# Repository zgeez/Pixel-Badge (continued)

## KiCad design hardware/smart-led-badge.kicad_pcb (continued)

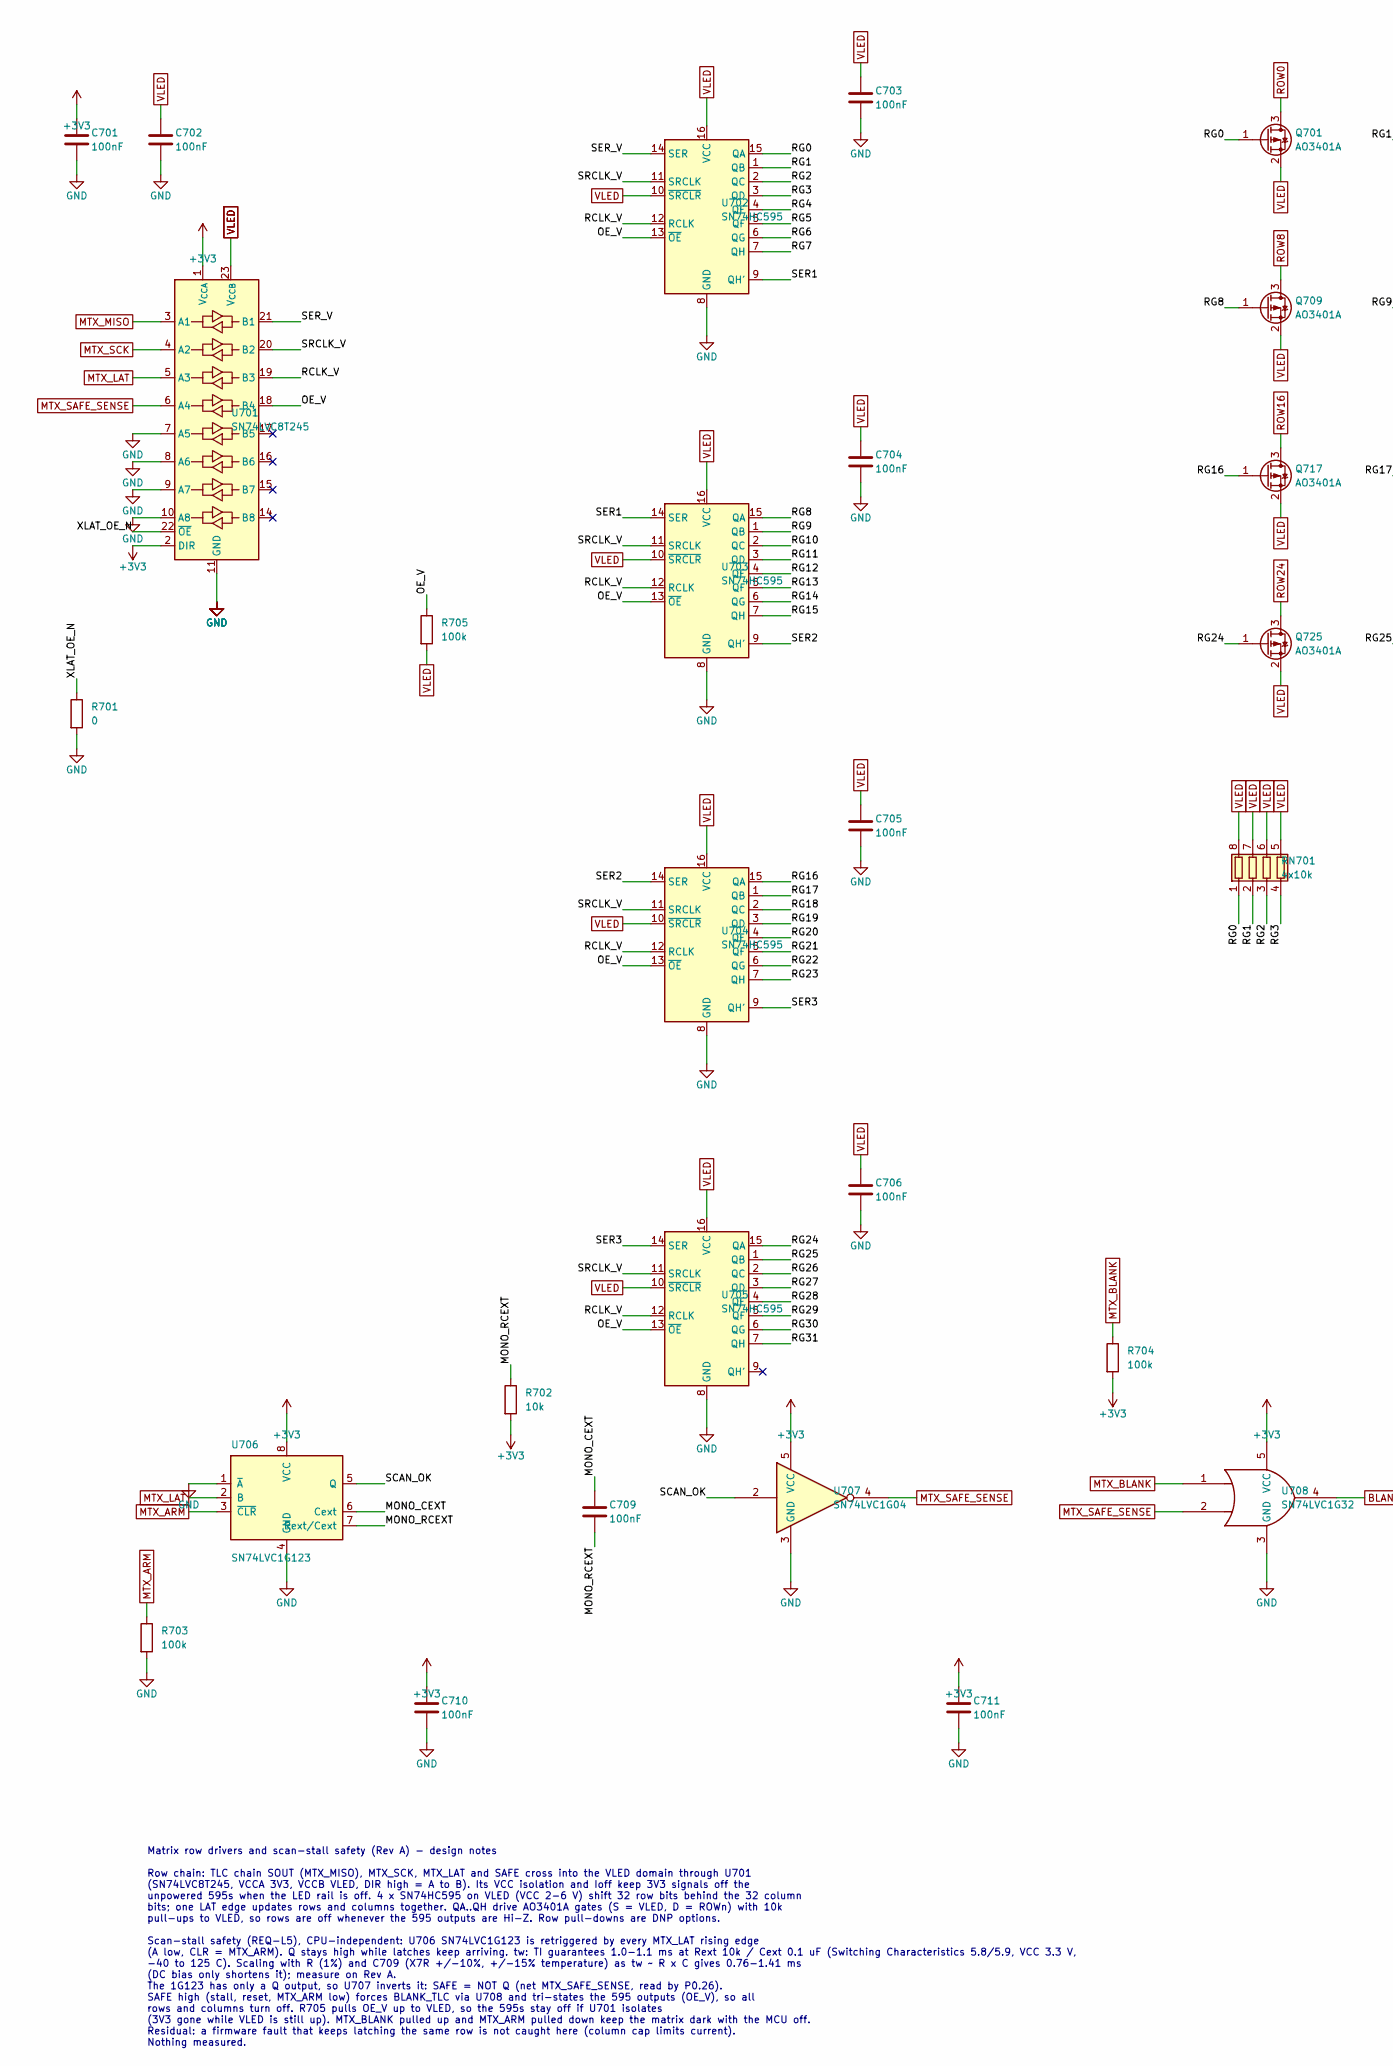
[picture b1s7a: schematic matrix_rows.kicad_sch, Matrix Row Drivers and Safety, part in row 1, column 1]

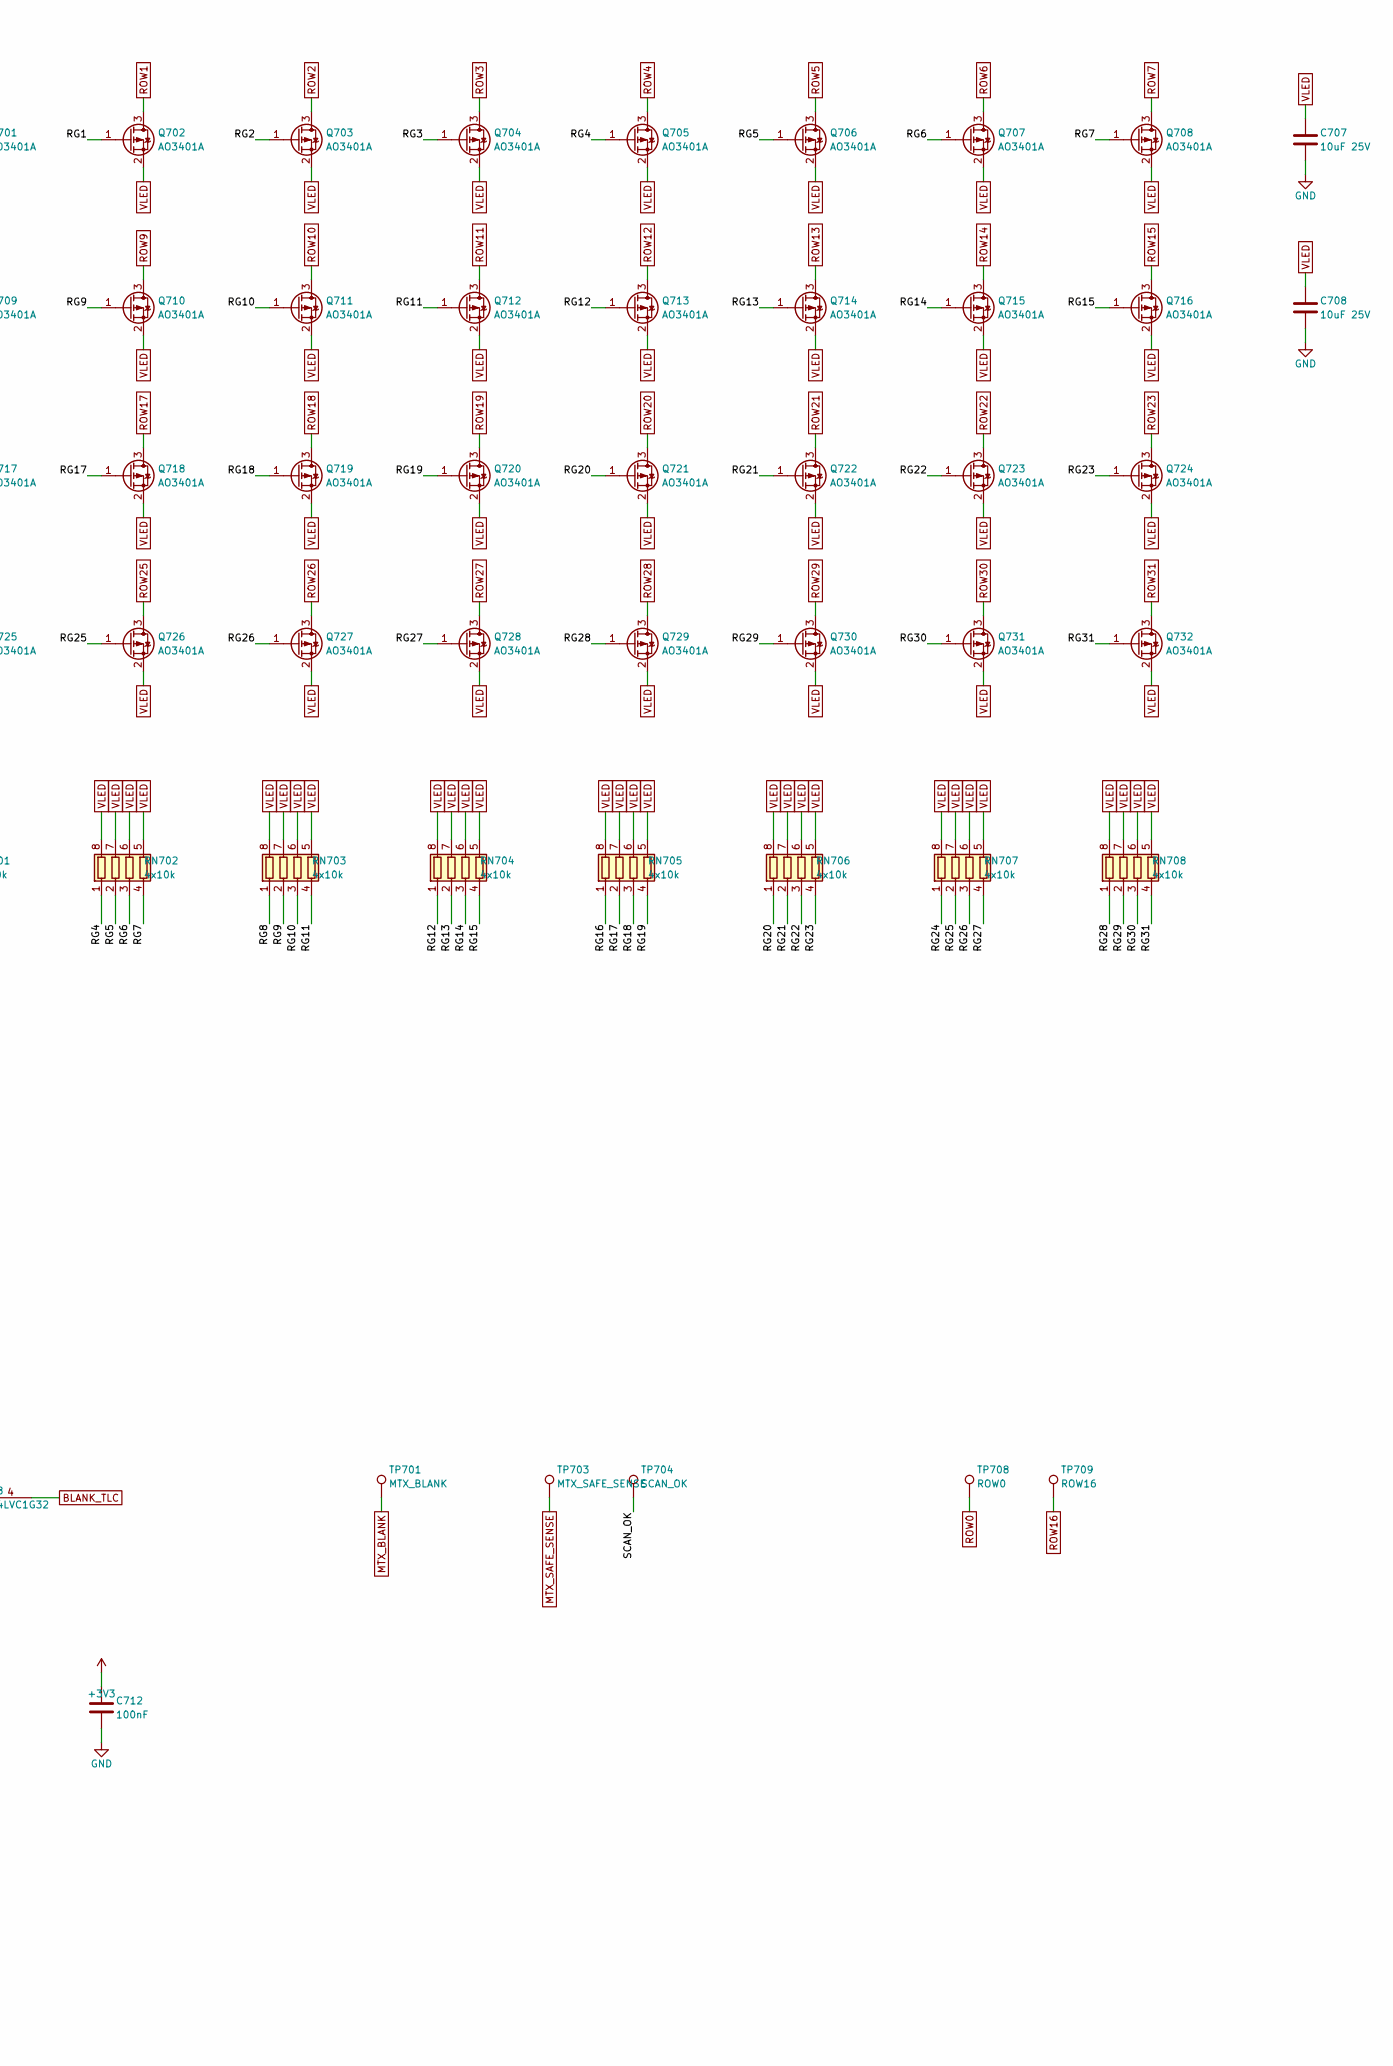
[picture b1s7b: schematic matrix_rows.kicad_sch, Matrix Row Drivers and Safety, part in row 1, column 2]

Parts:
C701, C702, C703, C704, C705, C706, C709, C710, C711, C712: 100nF; C_0402_1005Metric; MPN CL05B104KO5NNNC; LCSC C1525
C707, C708: 10uF 25V; C_0805_2012Metric; MPN CL21A106KAYNNNE; LCSC C15850
Q701, Q702, Q703, Q704, Q705, Q706, Q707, Q708, Q709, Q710, Q711, Q712, Q713, Q714, Q715, Q716, Q717, Q718, Q719, Q720, Q721, Q722, Q723, Q724, Q725, Q726, Q727, Q728, Q729, Q730, Q731, Q732: AO3401A; SOT-23; MPN AO3401A; LCSC C15127
R701: 0; R_0402_1005Metric; MPN 0402WGF0000TCE; LCSC C17168
R702: 10k; R_0402_1005Metric; MPN 0402WGF1002TCE; LCSC C25744
R703, R704, R705: 100k; R_0402_1005Metric; MPN 0402WGF1003TCE; LCSC C25741
RN701, RN702, RN703, RN704, RN705, RN706, RN707, RN708: 4x10k; R_Array_Convex_4x0603; MPN 4D03WGJ0103T5E; LCSC C29718
TP701: MTX_BLANK; TestPoint_Pad_D1.0mm
TP703: MTX_SAFE_SENSE; TestPoint_Pad_D1.0mm
TP704: SCAN_OK; TestPoint_Pad_D1.0mm
TP708: ROW0; TestPoint_Pad_D1.0mm
TP709: ROW16; TestPoint_Pad_D1.0mm
U701: SN74LVC8T245; TSSOP-24_4.4x7.8mm_P0.65mm; MPN SN74LVC8T245PWR; LCSC C27643
U702, U703, U704, U705: SN74HC595; TSSOP-16_4.4x5mm_P0.65mm; MPN SN74HC595PWR; LCSC C273642
U706: SN74LVC1G123; SSOP-8_2.95x2.8mm_P0.65mm; MPN SN74LVC1G123DCTR; LCSC C123302
U707: SN74LVC1G04; SOT-23-5; MPN SN74LVC1G04DBVR; LCSC C7827
U708: SN74LVC1G32; SOT-23-5; MPN SN74LVC1G32DBVR; LCSC C10096

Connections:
+3V3: C701.1, C710.1, C711.1, C712.1, R702.2, R704.2, U701.1 (V_{CCA}), U701.2 (DIR), U706.8 (VCC), U707.5 (VCC), U708.5 (VCC); also elsewhere on the board
/Matrix Row Drivers and Safety/MONO_CEXT: C709.1, U706.6 (Cext)
/Matrix Row Drivers and Safety/MONO_RCEXT: C709.2, R702.1, U706.7 (Rext/Cext)
/Matrix Row Drivers and Safety/OE_V: R705.1, U701.18 (B4), U702.13 (~OE), U703.13 (~OE), U704.13 (~OE), U705.13 (~OE)
/Matrix Row Drivers and Safety/RCLK_V: U701.19 (B3), U702.12 (RCLK), U703.12 (RCLK), U704.12 (RCLK), U705.12 (RCLK)
/Matrix Row Drivers and Safety/RG0: Q701.1 (G), RN701.1 (R1.1), U702.15 (QA)
/Matrix Row Drivers and Safety/RG1: Q702.1 (G), RN701.2 (R2.1), U702.1 (QB)
/Matrix Row Drivers and Safety/RG2: Q703.1 (G), RN701.3 (R3.1), U702.2 (QC)
/Matrix Row Drivers and Safety/RG3: Q704.1 (G), RN701.4 (R4.1), U702.3 (QD)
/Matrix Row Drivers and Safety/RG4: Q705.1 (G), RN702.1 (R1.1), U702.4 (QE)
/Matrix Row Drivers and Safety/RG5: Q706.1 (G), RN702.2 (R2.1), U702.5 (QF)
/Matrix Row Drivers and Safety/RG6: Q707.1 (G), RN702.3 (R3.1), U702.6 (QG)
/Matrix Row Drivers and Safety/RG7: Q708.1 (G), RN702.4 (R4.1), U702.7 (QH)
/Matrix Row Drivers and Safety/RG8: Q709.1 (G), RN703.1 (R1.1), U703.15 (QA)
/Matrix Row Drivers and Safety/RG9: Q710.1 (G), RN703.2 (R2.1), U703.1 (QB)
/Matrix Row Drivers and Safety/RG10: Q711.1 (G), RN703.3 (R3.1), U703.2 (QC)
/Matrix Row Drivers and Safety/RG11: Q712.1 (G), RN703.4 (R4.1), U703.3 (QD)
/Matrix Row Drivers and Safety/RG12: Q713.1 (G), RN704.1 (R1.1), U703.4 (QE)
/Matrix Row Drivers and Safety/RG13: Q714.1 (G), RN704.2 (R2.1), U703.5 (QF)
/Matrix Row Drivers and Safety/RG14: Q715.1 (G), RN704.3 (R3.1), U703.6 (QG)
/Matrix Row Drivers and Safety/RG15: Q716.1 (G), RN704.4 (R4.1), U703.7 (QH)
/Matrix Row Drivers and Safety/RG16: Q717.1 (G), RN705.1 (R1.1), U704.15 (QA)
/Matrix Row Drivers and Safety/RG17: Q718.1 (G), RN705.2 (R2.1), U704.1 (QB)
/Matrix Row Drivers and Safety/RG18: Q719.1 (G), RN705.3 (R3.1), U704.2 (QC)
/Matrix Row Drivers and Safety/RG19: Q720.1 (G), RN705.4 (R4.1), U704.3 (QD)
/Matrix Row Drivers and Safety/RG20: Q721.1 (G), RN706.1 (R1.1), U704.4 (QE)
/Matrix Row Drivers and Safety/RG21: Q722.1 (G), RN706.2 (R2.1), U704.5 (QF)
/Matrix Row Drivers and Safety/RG22: Q723.1 (G), RN706.3 (R3.1), U704.6 (QG)
/Matrix Row Drivers and Safety/RG23: Q724.1 (G), RN706.4 (R4.1), U704.7 (QH)
/Matrix Row Drivers and Safety/RG24: Q725.1 (G), RN707.1 (R1.1), U705.15 (QA)
/Matrix Row Drivers and Safety/RG25: Q726.1 (G), RN707.2 (R2.1), U705.1 (QB)
/Matrix Row Drivers and Safety/RG26: Q727.1 (G), RN707.3 (R3.1), U705.2 (QC)
/Matrix Row Drivers and Safety/RG27: Q728.1 (G), RN707.4 (R4.1), U705.3 (QD)
/Matrix Row Drivers and Safety/RG28: Q729.1 (G), RN708.1 (R1.1), U705.4 (QE)
/Matrix Row Drivers and Safety/RG29: Q730.1 (G), RN708.2 (R2.1), U705.5 (QF)
/Matrix Row Drivers and Safety/RG30: Q731.1 (G), RN708.3 (R3.1), U705.6 (QG)
/Matrix Row Drivers and Safety/RG31: Q732.1 (G), RN708.4 (R4.1), U705.7 (QH)
/Matrix Row Drivers and Safety/SCAN_OK: TP704.1, U706.5 (Q), U707.2
/Matrix Row Drivers and Safety/SER1: U702.9 (QH'), U703.14 (SER)
/Matrix Row Drivers and Safety/SER2: U703.9 (QH'), U704.14 (SER)
/Matrix Row Drivers and Safety/SER3: U704.9 (QH'), U705.14 (SER)
/Matrix Row Drivers and Safety/SER_V: U701.21 (B1), U702.14 (SER)
/Matrix Row Drivers and Safety/SRCLK_V: U701.20 (B2), U702.11 (SRCLK), U703.11 (SRCLK), U704.11 (SRCLK), U705.11 (SRCLK)
/Matrix Row Drivers and Safety/XLAT_OE_N: R701.1, U701.22 (~OE)
BLANK_TLC: U708.4; also elsewhere on the board
GND: C701.2, C702.2, C703.2, C704.2, C705.2, C706.2, C707.2, C708.2, C710.2, C711.2, C712.2, R701.2, R703.2, U701.7 (A5), U701.8 (A6), U701.9 (A7), U701.10 (A8), U701.11 (GND), U701.12 (GND), U701.13 (GND), U702.8 (GND), U703.8 (GND), U704.8 (GND), U705.8 (GND), U706.1 (~A), U706.4 (GND), U707.3 (GND), U708.3 (GND); also elsewhere on the board
MTX_ARM: R703.1, U706.3 (~CLR); also elsewhere on the board
MTX_BLANK: R704.1, TP701.1, U708.1; also elsewhere on the board
MTX_LAT: U701.5 (A3), U706.2 (B); also elsewhere on the board
MTX_MISO: U701.3 (A1); also elsewhere on the board
MTX_SAFE_SENSE: TP703.1, U701.6 (A4), U707.4, U708.2; also elsewhere on the board
MTX_SCK: U701.4 (A2); also elsewhere on the board
ROW0: Q701.3 (D), TP708.1; also elsewhere on the board
ROW1: Q702.3 (D); also elsewhere on the board
ROW2: Q703.3 (D); also elsewhere on the board
ROW3: Q704.3 (D); also elsewhere on the board
ROW4: Q705.3 (D); also elsewhere on the board
ROW5: Q706.3 (D); also elsewhere on the board
ROW6: Q707.3 (D); also elsewhere on the board
ROW7: Q708.3 (D); also elsewhere on the board
ROW8: Q709.3 (D); also elsewhere on the board
ROW9: Q710.3 (D); also elsewhere on the board
ROW10: Q711.3 (D); also elsewhere on the board
ROW11: Q712.3 (D); also elsewhere on the board
ROW12: Q713.3 (D); also elsewhere on the board
ROW13: Q714.3 (D); also elsewhere on the board
ROW14: Q715.3 (D); also elsewhere on the board
ROW15: Q716.3 (D); also elsewhere on the board
ROW16: Q717.3 (D), TP709.1; also elsewhere on the board
ROW17: Q718.3 (D); also elsewhere on the board
ROW18: Q719.3 (D); also elsewhere on the board
ROW19: Q720.3 (D); also elsewhere on the board
ROW20: Q721.3 (D); also elsewhere on the board
ROW21: Q722.3 (D); also elsewhere on the board
ROW22: Q723.3 (D); also elsewhere on the board
ROW23: Q724.3 (D); also elsewhere on the board
ROW24: Q725.3 (D); also elsewhere on the board
ROW25: Q726.3 (D); also elsewhere on the board
ROW26: Q727.3 (D); also elsewhere on the board
ROW27: Q728.3 (D); also elsewhere on the board
ROW28: Q729.3 (D); also elsewhere on the board
ROW29: Q730.3 (D); also elsewhere on the board
ROW30: Q731.3 (D); also elsewhere on the board
ROW31: Q732.3 (D); also elsewhere on the board
VLED: C702.1, C703.1, C704.1, C705.1, C706.1, C707.1, C708.1, Q701.2 (S), Q702.2 (S), Q703.2 (S), Q704.2 (S), Q705.2 (S), Q706.2 (S), Q707.2 (S), Q708.2 (S), Q709.2 (S), Q710.2 (S), Q711.2 (S), Q712.2 (S), Q713.2 (S), Q714.2 (S), Q715.2 (S), Q716.2 (S), Q717.2 (S), Q718.2 (S), Q719.2 (S), Q720.2 (S), Q721.2 (S), Q722.2 (S), Q723.2 (S), Q724.2 (S), Q725.2 (S), Q726.2 (S), Q727.2 (S), Q728.2 (S), Q729.2 (S), Q730.2 (S), Q731.2 (S), Q732.2 (S), R705.2, RN701.5 (R4.2), RN701.6 (R3.2), RN701.7 (R2.2), RN701.8 (R1.2), RN702.5 (R4.2), RN702.6 (R3.2), RN702.7 (R2.2), RN702.8 (R1.2), RN703.5 (R4.2), RN703.6 (R3.2), RN703.7 (R2.2), RN703.8 (R1.2), RN704.5 (R4.2), RN704.6 (R3.2), RN704.7 (R2.2), RN704.8 (R1.2), RN705.5 (R4.2), RN705.6 (R3.2), RN705.7 (R2.2), RN705.8 (R1.2), RN706.5 (R4.2), RN706.6 (R3.2), RN706.7 (R2.2), RN706.8 (R1.2), RN707.5 (R4.2), RN707.6 (R3.2), RN707.7 (R2.2), RN707.8 (R1.2), RN708.5 (R4.2), RN708.6 (R3.2), RN708.7 (R2.2), RN708.8 (R1.2), U701.23 (V_{CCB}), U701.24 (V_{CCB}), U702.10 (~SRCLR), U702.16 (VCC), U703.10 (~SRCLR), U703.16 (VCC), U704.10 (~SRCLR), U704.16 (VCC), U705.10 (~SRCLR), U705.16 (VCC); also elsewhere on the board

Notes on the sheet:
Matrix row drivers and scan-stall safety (Rev A) - design notes Row chain: TLC chain SOUT (MTX_MISO), MTX_SCK, MTX_LAT and SAFE cross into the VLED domain through U701 (SN74LVC8T245, VCCA 3V3, VCCB VLED, DIR high = A to B). Its VCC isolation and Ioff keep 3V3 signals off the unpowered 595s when the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

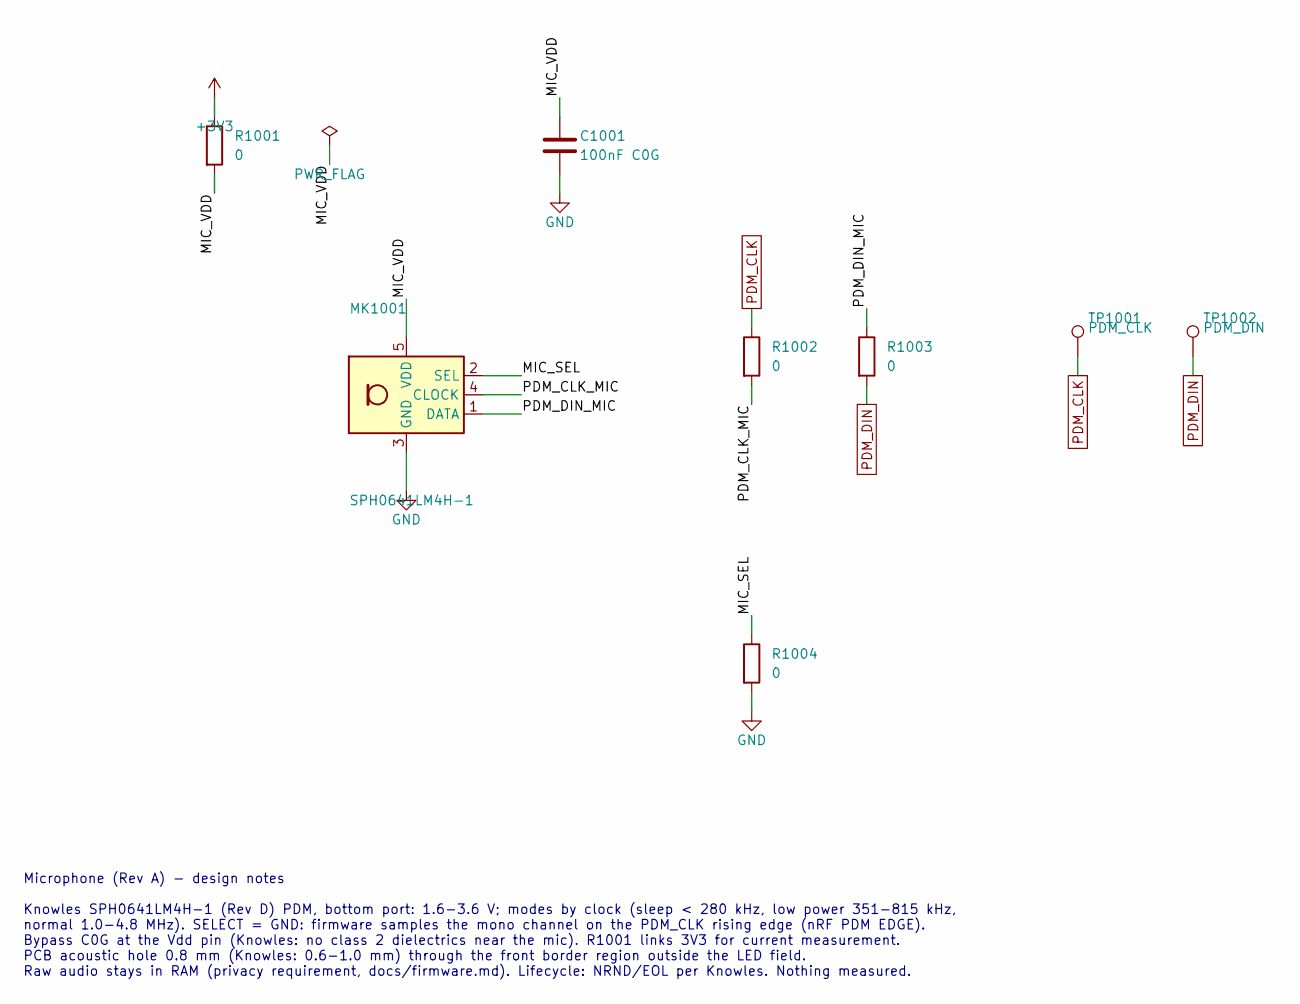
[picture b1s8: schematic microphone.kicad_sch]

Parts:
C1001: 100nF C0G; C_1206_3216Metric; MPN 1206N104J500CT; LCSC C170182
MK1001: SPH0641LM4H-1; Knowles_LGA-5_3.5x2.65mm_Hole0.6mm; MPN SPH0641LM4H-1; LCSC C497724
R1001, R1002, R1003, R1004: 0; R_0402_1005Metric; MPN 0402WGF0000TCE; LCSC C17168
TP1001: PDM_CLK; TestPoint_Pad_D1.0mm
TP1002: PDM_DIN; TestPoint_Pad_D1.0mm

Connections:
+3V3: R1001.1; also elsewhere on the board
/Microphone/MIC_SEL: MK1001.2 (SEL), R1004.1
/Microphone/MIC_VDD: C1001.1, MK1001.5 (VDD), R1001.2
/Microphone/PDM_CLK_MIC: MK1001.4 (CLOCK), R1002.2
/Microphone/PDM_DIN_MIC: MK1001.1 (DATA), R1003.1
GND: C1001.2, MK1001.3 (GND), R1004.2; also elsewhere on the board
PDM_CLK: R1002.1, TP1001.1; also elsewhere on the board
PDM_DIN: R1003.2, TP1002.1; also elsewhere on the board

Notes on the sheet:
Microphone (Rev A) - design notes Knowles SPH0641LM4H-1 (Rev D) PDM, bottom port: 1.6-3.6 V; modes by clock (sleep < 280 kHz, low power 351-815 kHz, normal 1.0-4.8 MHz). SELECT = GND: firmware samples the mono channel on the PDM_CLK rising edge (nRF PDM EDGE). Bypass C0G at the Vdd pin (Knowles: no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

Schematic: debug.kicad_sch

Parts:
J501: SWD 2x5 1.27mm; PinHeader_2x05_P1.27mm_Vertical_SMD; MPN HX PZ1.27-2x5P TP; LCSC C41376037

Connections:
+3V3: J501.1 (VTref); also elsewhere on the board
GND: J501.3 (GND), J501.5 (GND), J501.9 (GNDDetect); also elsewhere on the board
SWDCLK: J501.4 (SWCLK/TCK); also elsewhere on the board
SWDIO: J501.2 (SWDIO/TMS); also elsewhere on the board
nRESET: J501.10 (~RESET); also elsewhere on the board

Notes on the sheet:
Debug (Rev A) - design notes J501: ARM Cortex 10-pin SWD header (2 x 5, 1.27 mm) to the nRF5340 DK debug out (P19) by a 10-pin flat cable. Pin 3 = GND selects the external target. Voltages must match: run the DK at 3.3 V from P21 (SW10 VEXT->nRF ON, SW9 = VDD; DK on USB alone is 3.0 V). Keep DK SB4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
